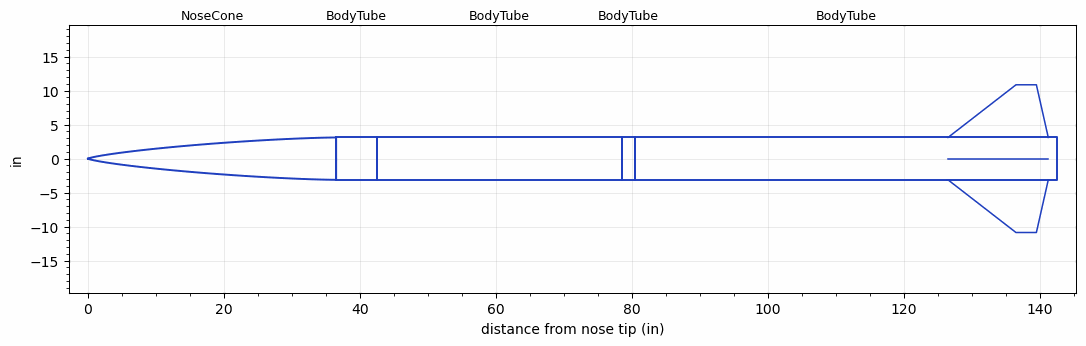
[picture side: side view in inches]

<RASAeroDocument>
 <FileVersion>2</FileVersion>
 <RocketDesign>
  <NoseCone>
   <Length>36.5</Length>
   <Diameter>6.23</Diameter>
   <Shape>Von Karman Ogive</Shape>
   <BluntRadius>0.075</BluntRadius>
   <Location>0</Location>
  </NoseCone>
  <BodyTube>
   <Length>6</Length>
   <Diameter>6.23</Diameter>
   <Location>36.5</Location>
  </BodyTube>
  <BodyTube>
   <Length>36</Length>
   <Diameter>6.23</Diameter>
   <Location>42.5</Location>
  </BodyTube>
  <BodyTube>
   <Length>2</Length>
   <Diameter>6.23</Diameter>
   <Location>78.5</Location>
  </BodyTube>
  <BodyTube>
   <Length>62</Length>
   <Diameter>6.23</Diameter>
   <RailGuideDiameter>0.5</RailGuideDiameter>
   <RailGuideHeight>0.56</RailGuideHeight>
   <Location>80.5</Location>
   <Fin>
    <Count>4</Count>
    <Chord>14.75</Chord>
    <Span>7.75</Span>
    <SweepDistance>10</SweepDistance>
    <TipChord>3</TipChord>
    <Thickness>0.255</Thickness>
    <LERadius>0.025</LERadius>
    <Location>16</Location>
    <AirfoilSection>Rounded</AirfoilSection>
    <FX1>1</FX1>
    <FX3>1</FX3>
   </Fin>
  </BodyTube>
  <Surface>Smooth Paint</Surface>
  <ModifiedBarrowman>False</ModifiedBarrowman>
  <Turbulence>False</Turbulence>
  <UseBooster1>False</UseBooster1>
  <UseBooster2>False</UseBooster2>
  <Comments>Includes new fin geometry to remove tip rake angle to allow for more accurate RasAero simluation verification</Comments>
 </RocketDesign>
 <LaunchSite>
  <Altitude>0</Altitude>
  <Pressure>28.26</Pressure>
  <RodAngle>5</RodAngle>
  <RodLength>17</RodLength>
  <Temperature>81</Temperature>
  <WindSpeed>16</WindSpeed>
 </LaunchSite>
 <Recovery>
  <Altitude1>1500</Altitude1>
  <Altitude2>1500</Altitude2>
  <DeviceType1>Parachute</DeviceType1>
  <DeviceType2>Parachute</DeviceType2>
  <Event1>True</Event1>
  <Event2>True</Event2>
  <Size1>36</Size1>
  <Size2>120</Size2>
  <EventType1>Apogee</EventType1>
  <EventType2>Altitude</EventType2>
  <CD1>1.16</CD1>
  <CD2>1.16</CD2>
 </Recovery>
 <SimulationList>
  <Simulation>
   <SustainerEngine>O3443  (WVUER2025)</SustainerEngine>
   <SustainerLaunchWt>121</SustainerLaunchWt>
   <SustainerNozzleDiameter>2.4</SustainerNozzleDiameter>
   <SustainerCG>101</SustainerCG>
   <SustainerIgnitionDelay>0</SustainerIgnitionDelay>
   <Booster1SeparationDelay>0</Booster1SeparationDelay>
   <Booster1IgnitionDelay>0</Booster1IgnitionDelay>
   <IncludeBooster1>False</IncludeBooster1>
   <Booster2Delay>0</Booster2Delay>
   <IncludeBooster2>False</IncludeBooster2>
   <TimetoApogee>41.78899</TimetoApogee>
   <MaxAltitude>30019.95</MaxAltitude>
   <MaxVelocity>1699.124</MaxVelocity>
   <OptimumWt>75.42841</OptimumWt>
   <OptimumMaxAlt>75.42841</OptimumMaxAlt>
  </Simulation>
  <Simulation>
   <SustainerLaunchWt>138.5684</SustainerLaunchWt>
   <SustainerCG>94.979</SustainerCG>
   <SustainerIgnitionDelay>0</SustainerIgnitionDelay>
   <Booster1SeparationDelay>0</Booster1SeparationDelay>
   <Booster1IgnitionDelay>0</Booster1IgnitionDelay>
   <IncludeBooster1>False</IncludeBooster1>
   <Booster2Delay>0</Booster2Delay>
   <IncludeBooster2>False</IncludeBooster2>
  </Simulation>
  <Simulation>
   <SustainerLaunchWt>138.5684</SustainerLaunchWt>
   <SustainerCG>94.979</SustainerCG>
   <SustainerIgnitionDelay>0</SustainerIgnitionDelay>
   <Booster1SeparationDelay>0</Booster1SeparationDelay>
   <Booster1IgnitionDelay>0</Booster1IgnitionDelay>
   <IncludeBooster1>False</IncludeBooster1>
   <Booster2Delay>0</Booster2Delay>
   <IncludeBooster2>False</IncludeBooster2>
  </Simulation>
 </SimulationList>
</RASAeroDocument>
